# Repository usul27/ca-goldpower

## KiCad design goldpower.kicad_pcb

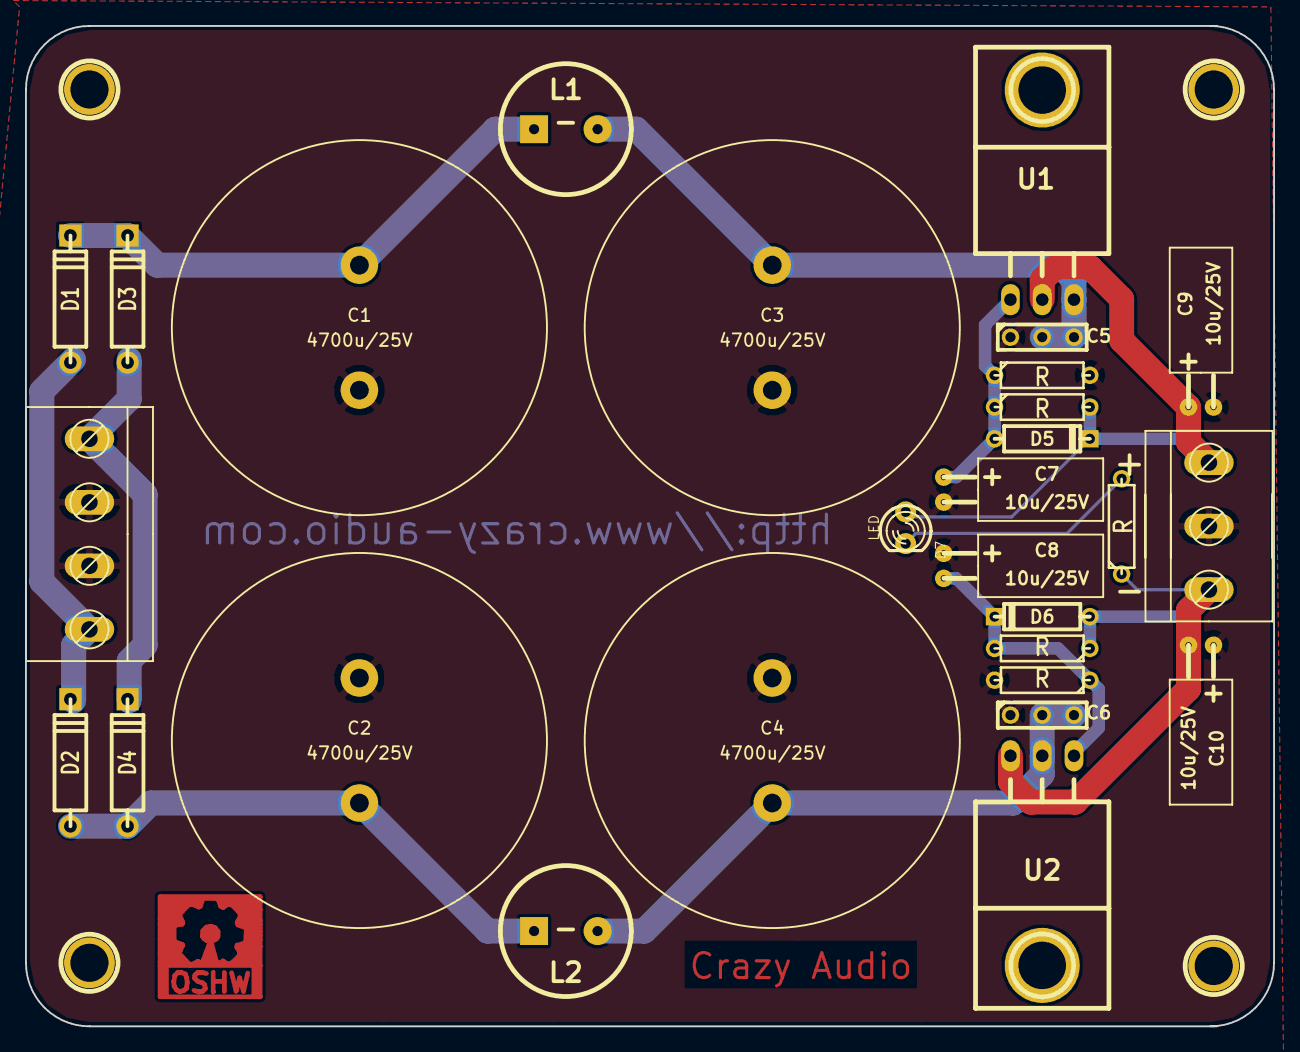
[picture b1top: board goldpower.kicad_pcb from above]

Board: 2 copper layers, 99.8 x 80.0 mm, 33 parts (0 on the bottom side), 12 nets.

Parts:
1PIN, 1PIN#2, 1PIN#3, 1PIN#4: P***; 1pin
C1, C2, C3, C4: 4700u/25V; CP_10_30
C5, C6: 100n; C1-1
C7, C8, C9, C10: 10u/25V; C2_D5x10
D1, D2, D3, D4: DIODE; D4
D5, D6: 1N4002; D3
D7: LED; LED-3MM
K1: CONN_3; AKL073-3
L1, L2: -; HFSRA_C
P1: CONN_4; AKL073-4
R1, R2, R3, R4, R5: R; R3
SYM: Symbol_OSHW-Logo_CopperTop_Negative_07Jul2012
U1: LM317T; TO-220_Neutral123_Horizontal
U2: LM337T; TO-220_Neutral123_Horizontal

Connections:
GND: C1.2, C2.1, C3.2, C4.1, C5.1, C6.1, C7.2, C8.1, C9.2, C10.1, K1.2, P1.2, P1.3, R1.2, R2.2
unnamed: C10.2, D6.1, K1.1, R4.1, R5.1, U2.3
unnamed: D3.1, D4.2, P1.1
unnamed: C8.2, D6.2, R2.1, R4.2, U2.1
unnamed: D7.2, R5.2
unnamed: C9.1, D5.2, D7.1, K1.3, R3.2, U1.2
unnamed: C1.1, D1.2, D3.2, L1.1
unnamed: C2.2, D2.1, D4.1, L2.1
unnamed: D1.1, D2.2, P1.4
unnamed: C7.1, D5.1, R1.1, R3.1, U1.1
unnamed: C3.1, C5.2, L1.2, U1.3
unnamed: C4.2, C6.2, L2.2, U2.2

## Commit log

2013-05-29 initial version
2013-05-29 First working version
2013-05-30 Slight changes, only 1 LED now
2013-06-04 two groundplanes now
